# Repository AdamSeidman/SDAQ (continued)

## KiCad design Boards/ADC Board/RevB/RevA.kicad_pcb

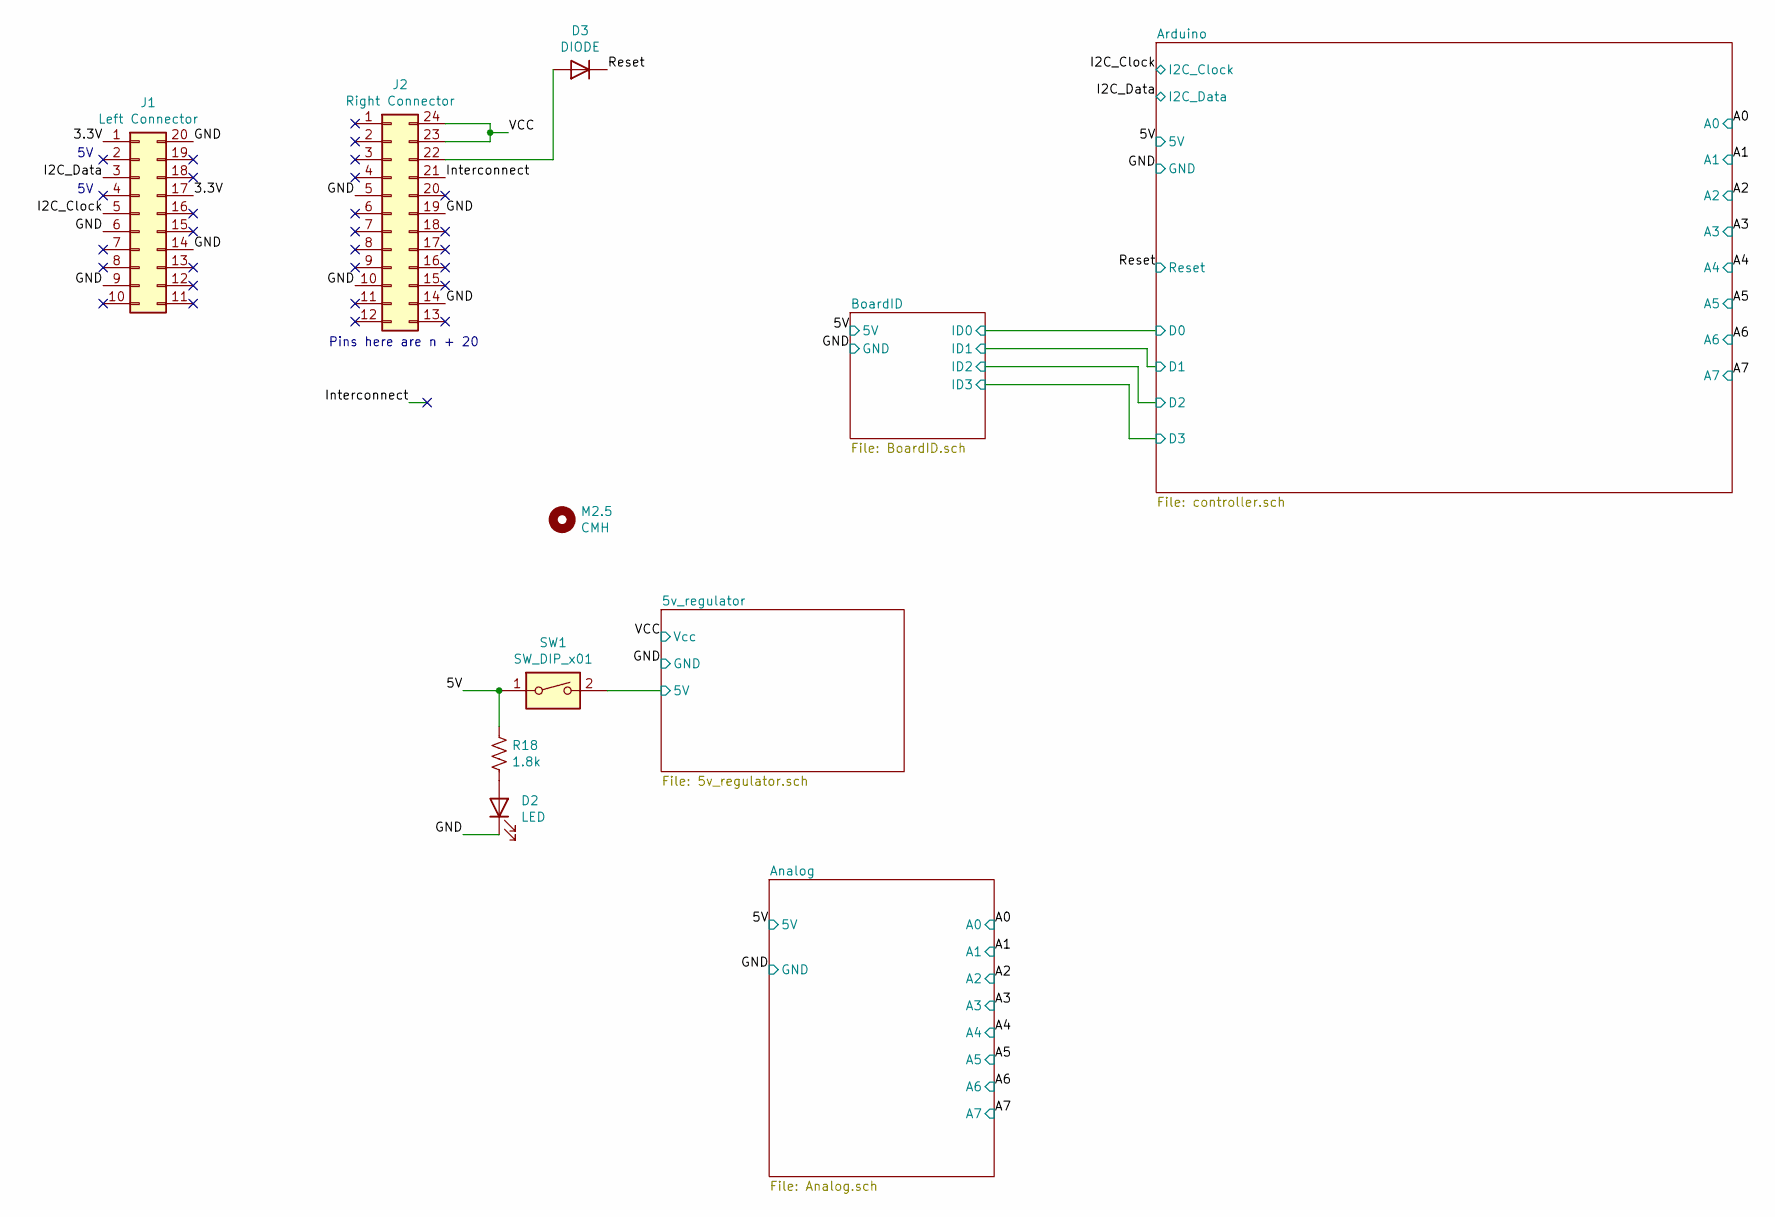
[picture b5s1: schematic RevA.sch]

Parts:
D2: LED; LED_1206_3216Metric
D3: DIODE; D_SMA
J1: Left Connector; PinHeader_2x10_P2.54mm_Vertical
J2: Right Connector; PinHeader_2x12_P2.54mm_Vertical
M2.5: CMH; MountingHole_2.7mm_M2.5
R18: 1.8k; R_0603_1608Metric
SW1: SW_DIP_x01; SW_DIP_SPSTx01_Slide_9.78x4.72mm_W8.61mm_P2.54mm

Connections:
/3.3V: J1.1, J1.17
/5V: R18.1, SW1.1; also elsewhere on the board
/5v_regulator/5V: SW1.2; also elsewhere on the board
/GND: D2.1 (K), J1.6, J1.9, J1.14, J1.20, J2.5, J2.10, J2.14, J2.19; also elsewhere on the board
/I2C_Clock: J1.5; also elsewhere on the board
/I2C_Data: J1.3; also elsewhere on the board
/Interconnect: J2.21
/Reset: D3.2 (K); also elsewhere on the board
/VCC: J2.23, J2.24; also elsewhere on the board
unnamed: D2.2 (A), R18.2
unnamed: D3.1 (A), J2.22

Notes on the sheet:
Pins here are n + 20

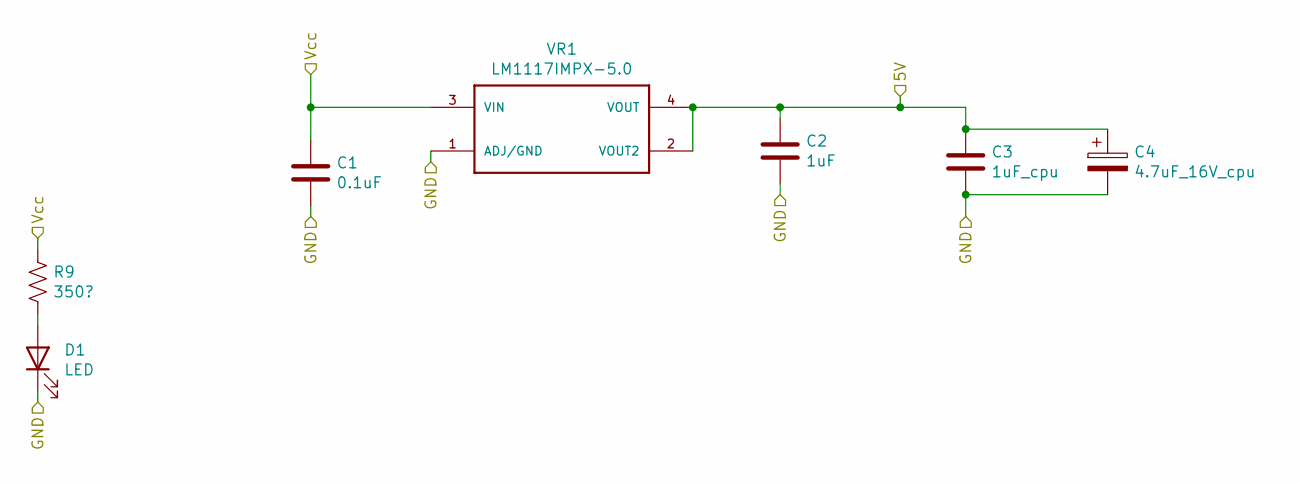
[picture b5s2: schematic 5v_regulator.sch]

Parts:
C1: 0.1uF; C_0603_1608Metric
C2: 1uF; C_0603_1608Metric
C3: 1uF_cpu; C_0603_1608Metric
C4: 4.7uF_16V_cpu; CP_EIA-3216-18_Kemet-A
D1: LED; LED_1206_3216Metric
R9: 350?; R_0603_1608Metric
VR1: LM1117IMPX-5.0; SOT230P700X180-4N

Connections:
/5v_regulator/5V: C2.1, C3.1, C4.1, VR1.2 (VOUT2), VR1.4 (VOUT); also elsewhere on the board
/GND: C1.2, C2.2, C3.2, C4.2, D1.1 (K), VR1.1 (ADJ/GND); also elsewhere on the board
/VCC: C1.1, R9.1, VR1.3 (VIN); also elsewhere on the board
unnamed: D1.2 (A), R9.2

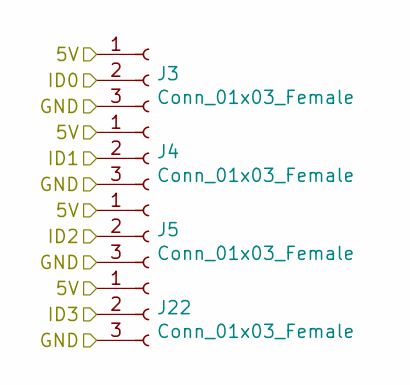
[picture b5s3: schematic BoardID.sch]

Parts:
J3, J4, J5, J22: Conn_01x03_Female; PinHeader_1x03_P1.27mm_Vertical

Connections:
/5V: J3.1, J4.1, J5.1, J22.1; also elsewhere on the board
/Arduino/D0: J3.2; also elsewhere on the board
/Arduino/D1: J4.2; also elsewhere on the board
/Arduino/D2: J5.2; also elsewhere on the board
/Arduino/D3: J22.2; also elsewhere on the board
/GND: J3.3, J4.3, J5.3, J22.3; also elsewhere on the board

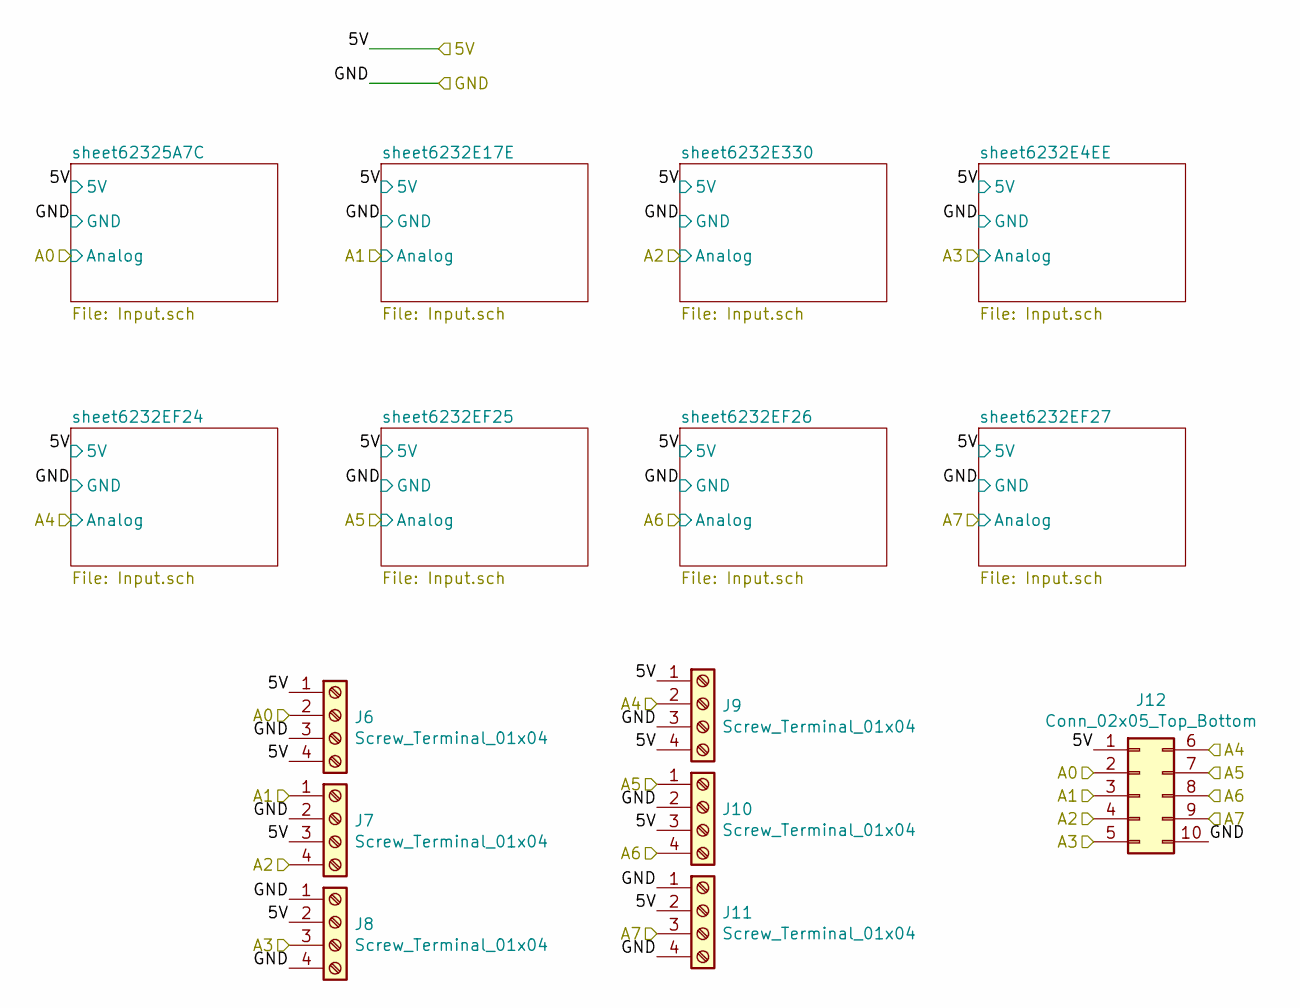
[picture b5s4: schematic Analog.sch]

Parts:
J6, J7, J8, J9, J10, J11: Screw_Terminal_01x04; 1984989
J12: Conn_02x05_Top_Bottom; PinHeader_2x05_P2.54mm_Vertical

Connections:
/5V: J6.1, J6.4, J7.3, J8.2, J9.1, J9.4, J10.3, J11.2, J12.1; also elsewhere on the board
/A0: J6.2, J12.2; also elsewhere on the board
/A1: J7.1, J12.3; also elsewhere on the board
/A2: J7.4, J12.4; also elsewhere on the board
/A3: J8.3, J12.5; also elsewhere on the board
/A4: J9.2, J12.6; also elsewhere on the board
/A5: J10.1, J12.7; also elsewhere on the board
/A6: J10.4, J12.8; also elsewhere on the board
/A7: J11.3, J12.9; also elsewhere on the board
/GND: J6.3, J7.2, J8.1, J8.4, J9.3, J10.2, J11.1, J11.4, J12.10; also elsewhere on the board

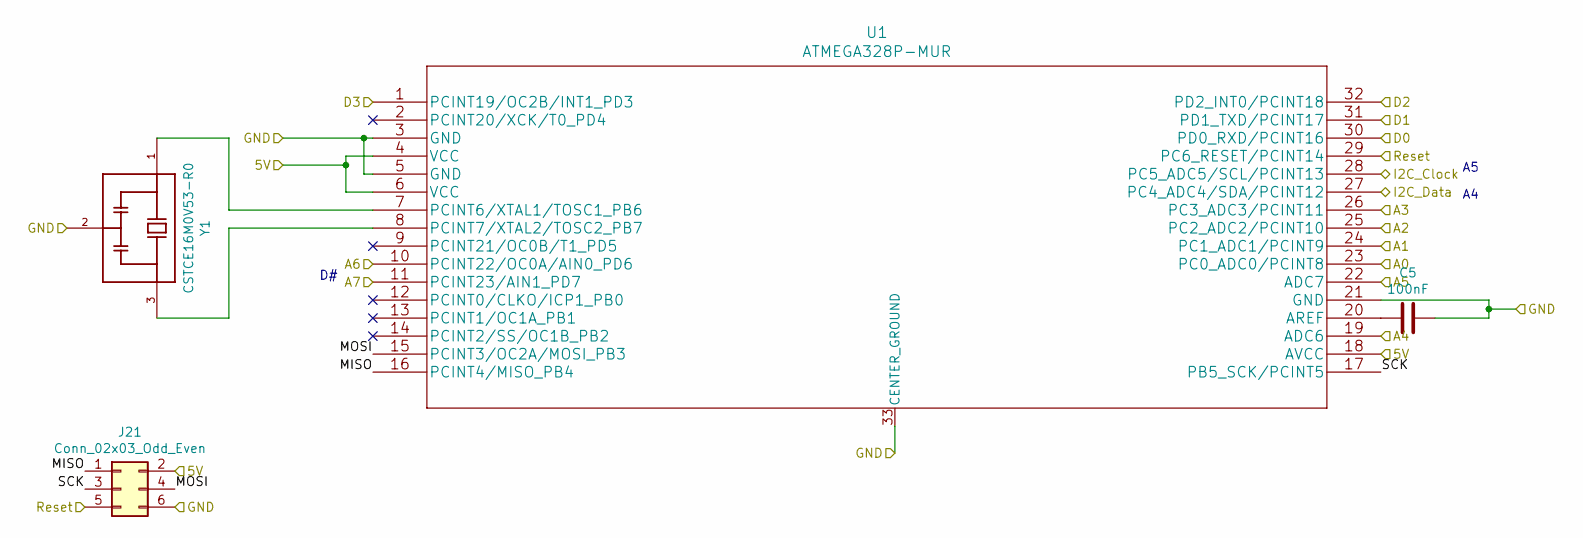
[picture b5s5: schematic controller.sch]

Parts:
C5: 100nF; C_0603_1608Metric
J21: Conn_02x03_Odd_Even; PinHeader_2x03_P2.54mm_Vertical
U1: ATMEGA328P-MUR
Y1: CSTCE16M0V53-R0

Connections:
/5V: J21.2, U1.4 (VCC), U1.6 (VCC), U1.18 (AVCC); also elsewhere on the board
/A0: U1.23 (PC0_ADC0/PCINT8); also elsewhere on the board
/A1: U1.24 (PC1_ADC1/PCINT9); also elsewhere on the board
/A2: U1.25 (PC2_ADC2/PCINT10); also elsewhere on the board
/A3: U1.26 (PC3_ADC3/PCINT11); also elsewhere on the board
/A4: U1.19 (ADC6); also elsewhere on the board
/A5: U1.22 (ADC7); also elsewhere on the board
/A6: U1.10 (PCINT22/OC0A/AIN0_PD6); also elsewhere on the board
/A7: U1.11 (PCINT23/AIN1_PD7); also elsewhere on the board
/Arduino/D0: U1.30 (PD0_RXD/PCINT16); also elsewhere on the board
/Arduino/D1: U1.31 (PD1_TXD/PCINT17); also elsewhere on the board
/Arduino/D2: U1.32 (PD2_INT0/PCINT18); also elsewhere on the board
/Arduino/D3: U1.1 (PCINT19/OC2B/INT1_PD3); also elsewhere on the board
/Arduino/MISO: J21.1, U1.16 (PCINT4/MISO_PB4)
/Arduino/MOSI: J21.4, U1.15 (PCINT3/OC2A/MOSI_PB3)
/Arduino/SCK: J21.3, U1.17 (PB5_SCK/PCINT5)
/GND: C5.1, J21.6, U1.3 (GND), U1.5 (GND), U1.21 (GND), U1.33 (CENTER_GROUND), Y1.2; also elsewhere on the board
/I2C_Clock: U1.28 (PC5_ADC5/SCL/PCINT13); also elsewhere on the board
/I2C_Data: U1.27 (PC4_ADC4/SDA/PCINT12); also elsewhere on the board
/Reset: J21.5, U1.29 (PC6_RESET/PCINT14); also elsewhere on the board
unnamed: C5.2, U1.20 (AREF)
unnamed: U1.7 (PCINT6/XTAL1/TOSC1_PB6), Y1.1
unnamed: U1.8 (PCINT7/XTAL2/TOSC2_PB7), Y1.3

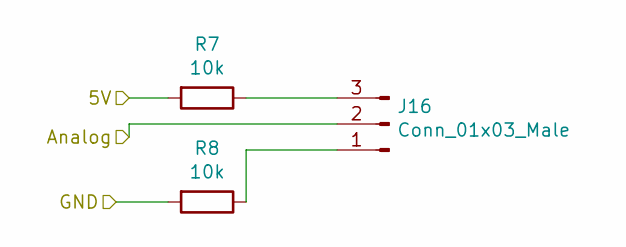
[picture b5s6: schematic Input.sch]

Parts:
J13: Conn_01x03_Male; PinHeader_1x03_P2.54mm_Vertical
R1, R2: 10k; R_0603_1608Metric

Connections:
/5V: R1.2; also elsewhere on the board
/A0: J13.2; also elsewhere on the board
/GND: R2.2; also elsewhere on the board
unnamed: J13.1, R2.1
unnamed: J13.3, R1.1

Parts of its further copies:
J14, J15, J16, J17, J18, J19, J20: Conn_01x03_Male; PinHeader_1x03_P2.54mm_Vertical
R3, R4, R5, R6, R7, R8, R10, R11, R12, R13, R14, R15, R16, R17: 10k; R_0603_1608Metric

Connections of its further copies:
/5V: R3.2, R5.2, R7.2, R10.2, R12.2, R14.2, R16.2; also elsewhere on the board
/A1: J14.2; also elsewhere on the board
/A2: J15.2; also elsewhere on the board
/A3: J16.2; also elsewhere on the board
/A4: J17.2; also elsewhere on the board
/A5: J18.2; also elsewhere on the board
/A6: J19.2; also elsewhere on the board
/A7: J20.2; also elsewhere on the board
/GND: R4.2, R6.2, R8.2, R11.2, R13.2, R15.2, R17.2; also elsewhere on the board
unnamed: J14.1, R4.1
unnamed: J14.3, R3.1
unnamed: J15.1, R6.1
unnamed: J15.3, R5.1
unnamed: J16.1, R8.1
unnamed: J16.3, R7.1
unnamed: J17.1, R11.1
unnamed: J17.3, R10.1
unnamed: J18.1, R13.1
unnamed: J18.3, R12.1
unnamed: J19.1, R15.1
unnamed: J19.3, R14.1
unnamed: J20.1, R17.1
unnamed: J20.3, R16.1

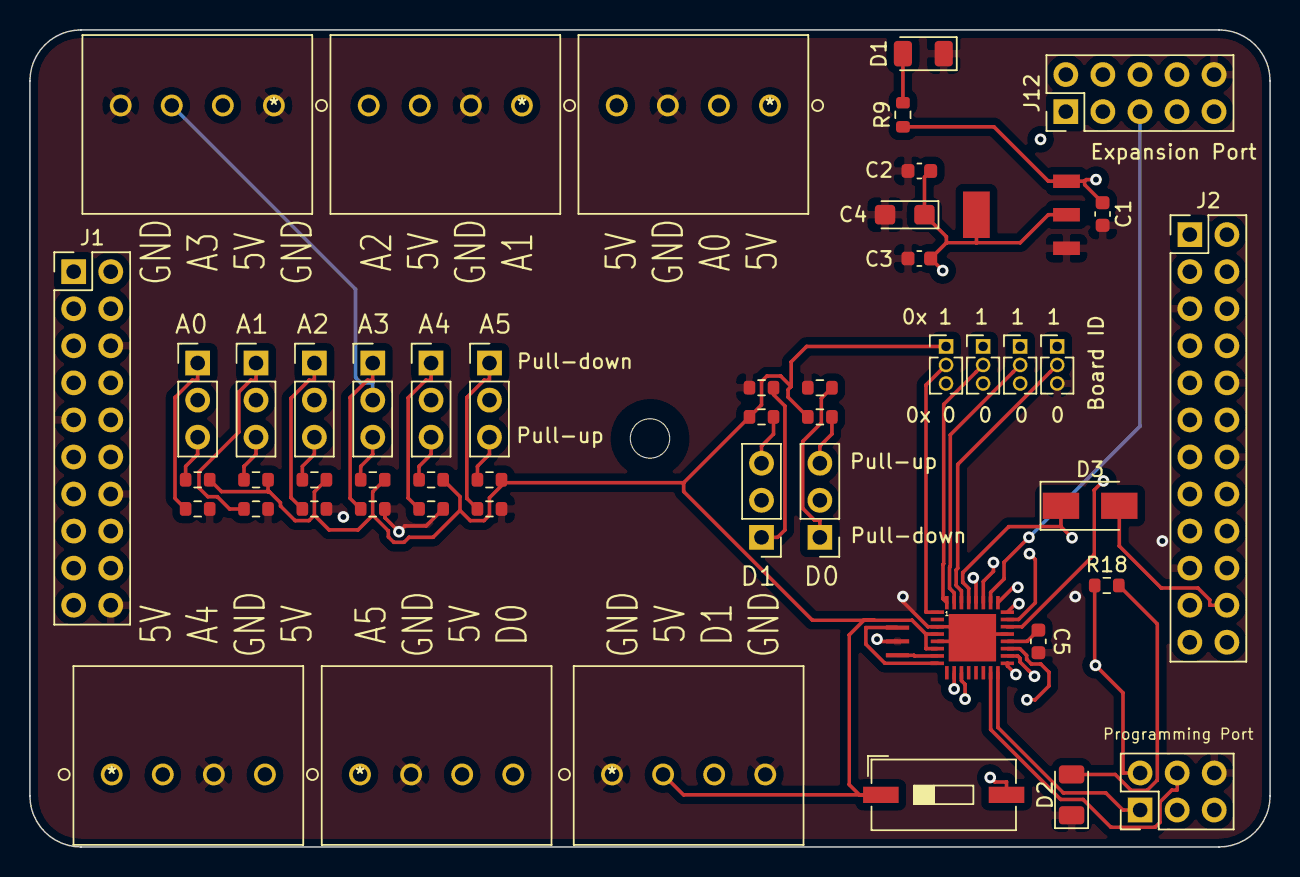
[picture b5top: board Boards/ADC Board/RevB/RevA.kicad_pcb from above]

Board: 4 copper layers, 85.0 x 56.0 mm, 53 parts (0 on the bottom side), 45 nets.

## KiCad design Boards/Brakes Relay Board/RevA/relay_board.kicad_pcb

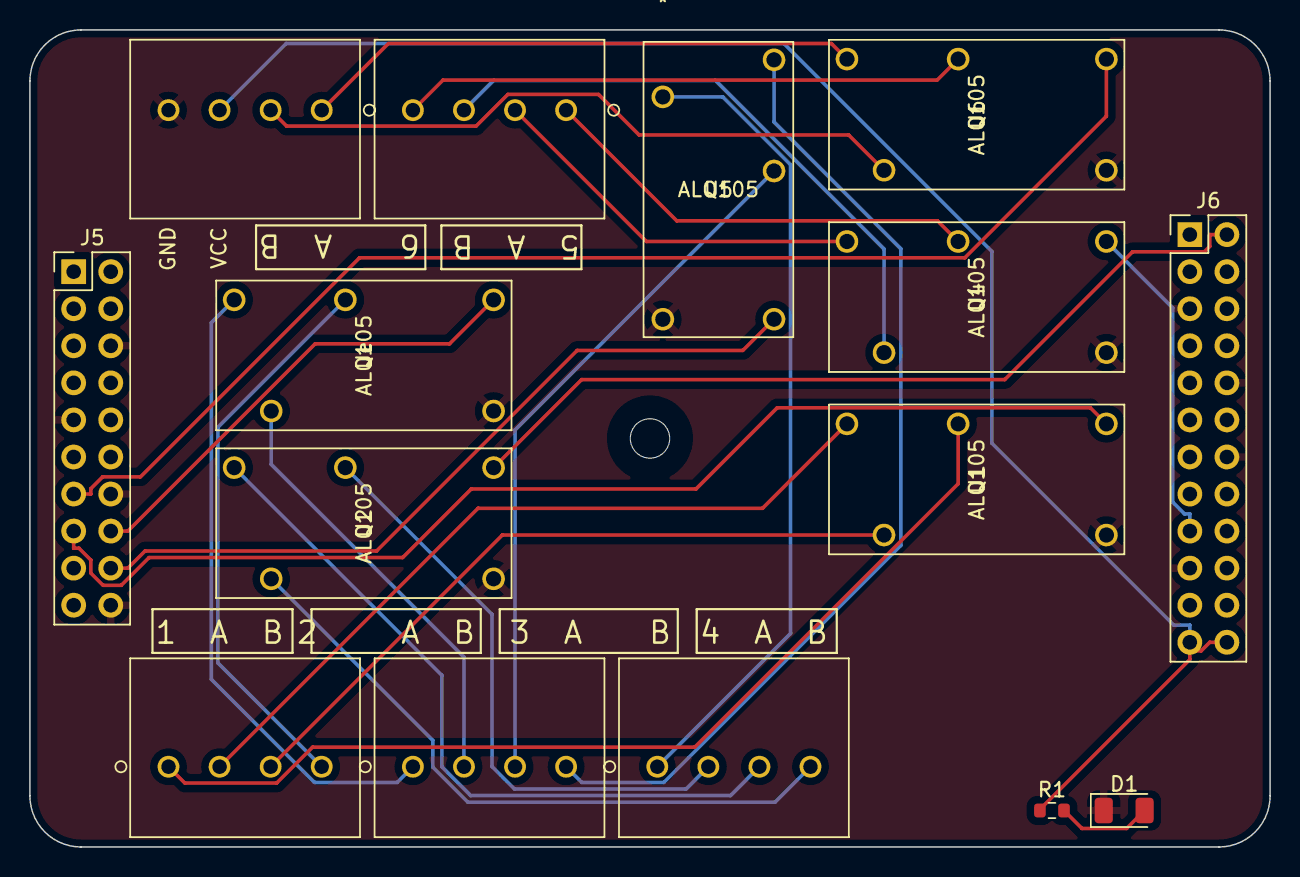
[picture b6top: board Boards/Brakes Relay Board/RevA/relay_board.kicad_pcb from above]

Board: 2 copper layers, 85.0 x 56.0 mm, 15 parts (0 on the bottom side), 27 nets.

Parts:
D1: LED; D_1206_3216Metric
J, J1, J2, J4, J7: Screw_Terminal_01x04; 1984989
J5: Conn_02x10_Counter_Clockwise; PinHeader_2x10_P2.54mm_Vertical
J6: Conn_02x12_Counter_Clockwise; PinHeader_2x12_P2.54mm_Vertical
R1: R; R_0603_1608Metric
U1, U2, U4, U5, U6: ALQ105
Ue: ALQ105

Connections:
/Ch1: J1.1, U1.2
/Ch1A: J1.2, U1.1
/Ch1B: J1.3, U1.5
/Ch2: J1.4, Ue.2
/Ch2A: J2.1, Ue.1
/Ch2B: J2.2, Ue.5
/Ch3: J2.3, U5.2
/Ch3A: J2.4, U5.1
/Ch3B: J.1, U5.5
/Ch4: J.2, U2.2
/Ch4A: J.3, U2.1
/Ch4B: J.4, U2.5
/Ch5: J4.1, U4.2
/Ch5A: J4.2, U4.1
/Ch5B: J4.3, U4.5
/Ch6: J4.4, U6.2
/Ch6A: J7.1, U6.1
/Ch6B: J7.2, U6.5
/GND: D1.1 (K), J5.6, J5.9, J5.14, J5.20, J6.5, J6.10, J6.14, J6.19, J7.4, U1.4, U2.4, U4.4, U5.4, U6.4, Ue.4
/R0: J5.15, U1.3
/R1: J5.16, Ue.3
/R2: J5.18, U5.3
/R3: J6.2, U2.3
/R4: J6.17, U4.3
/R5: J5.13, U6.3
/VCC: J6.23, J6.24, J7.3, R1.1
unnamed: D1.2 (A), R1.2

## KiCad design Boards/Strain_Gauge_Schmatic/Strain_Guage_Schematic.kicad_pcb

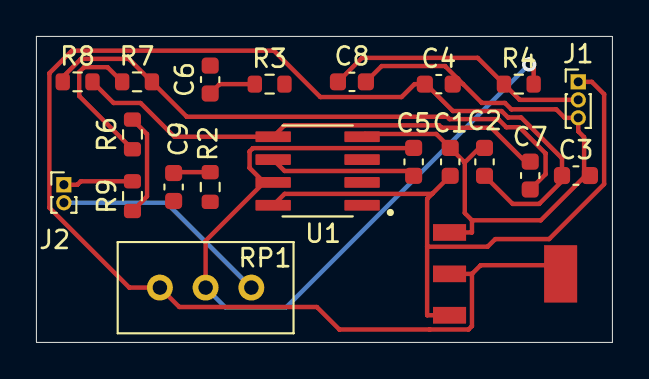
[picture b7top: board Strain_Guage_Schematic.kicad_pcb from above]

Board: 2 copper layers, 32.0 x 17.0 mm, 21 parts (0 on the bottom side), 14 nets.

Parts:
C1: 0.1uF; C_0603_1608Metric
C2: 1uF; C_0603_1608Metric
C3: 1uF_cpu; C_0603_1608Metric
C4: 4.7uF_16V_cpu; C_0603_1608Metric
C5, C6, C7, C8, C9: 100nF; C_0603_1608Metric
J1: Conn_01x03_Male; PinHeader_1x03_P1.00mm_Vertical
J2: Conn_01x02_Male; PinHeader_1x02_P1.00mm_Vertical
R2, R8, R9: 3.6k; R_0603_1608Metric
R3: 10k; R_0603_1608Metric
R4: 47k; R_0603_1608Metric
R6: 22k; R_0603_1608Metric
R7: 470k; R_0603_1608Metric
RP1: R_POT; Potentiometer_Bourns_3296W_Vertical
U1: LM358; SOIC127P599X175-8N
VR1: LM1117IMPX-5.0; SOT230P700X180-4N

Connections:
/Regulator/5V: C2.1, C3.1, C4.1, RP1.3, VR1.2, VR1.4
/Regulator/Vcc: C1.1, J1.1, VR1.3
GND: C1.2, C2.2, C3.2, C4.2, C8.2, J1.3, VR1.1
unnamed: C5.1, U1.6
unnamed: C5.2, R4.2, RP1.2, U1.7
unnamed: C6.1, R3.1
unnamed: C7.1, R7.2, R8.1
unnamed: C7.2, R8.2, U1.5
unnamed: C9.2, R2.1
unnamed: J2.1, R9.2
unnamed: J2.2, RP1.1
unnamed: R6.1, R7.1
unnamed: R6.2, R9.1
Out: C8.1, J1.2, R4.1

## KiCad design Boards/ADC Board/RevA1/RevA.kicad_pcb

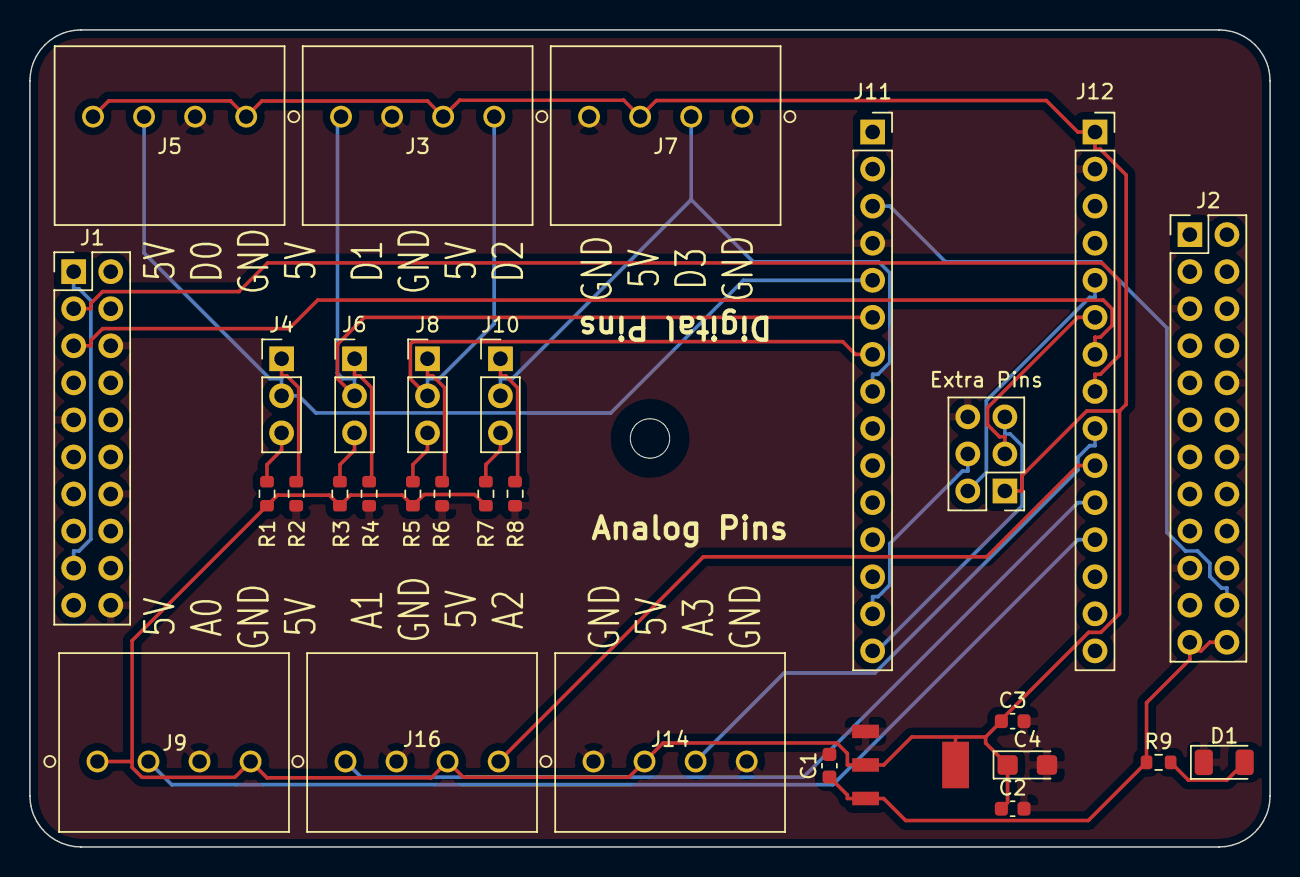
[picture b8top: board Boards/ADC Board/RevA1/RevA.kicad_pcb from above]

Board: 2 copper layers, 85.0 x 56.0 mm, 31 parts (0 on the bottom side), 28 nets.

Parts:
C1: 0.1uF; C_0603_1608Metric
C2: 1uF; C_0603_1608Metric
C3: 1uF_cpu; C_0603_1608Metric
C4: 4.7uF_16V_cpu; CP_EIA-3216-18_Kemet-A
D1: LED; LED_1206_3216Metric
J1: Left Connector; PinHeader_2x10_P2.54mm_Vertical
J2: Right Connector; PinHeader_2x12_P2.54mm_Vertical
J3, J5, J7, J9, J14, J16: Screw Terminals; 1984989
J4, J6, J8, J10: Jumper Terminals; PinHeader_1x03_P2.54mm_Vertical
J11: Arduino Nano L; PinSocket_1x15_P2.54mm_Vertical
J12: Arduino Nano R; PinSocket_1x15_P2.54mm_Vertical
J13: Extra Pins; PinHeader_2x03_P2.54mm_Vertical
M2.5: CMH; MountingHole_2.7mm_M2.5
R1, R2, R3, R4, R5, R6, R7, R8: 10k; R_0603_1608Metric
R9: 350?; R_0603_1608Metric
VR1: LM1117IMPX-5.0; SOT230P700X180-4N

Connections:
/3.3V: J1.1, J1.17
/5V: C2.1, C3.1, C4.1, J3.2, J5.1, J5.4, J7.3, J9.1, J9.4, J12.1, J13.1, J14.2, J16.3, R1.2, R3.2, R5.2, R7.2, VR1.2, VR1.4
/Analog_0: J9.2, J12.12
/Analog_1: J12.11, J16.1
/Analog_2: J12.10, J16.4
/Analog_3: J12.9, J14.3
/Controller/A6: J12.6, J13.3
/Controller/A7: J12.5, J13.2
/Controller/D11: J11.14, J13.4
/Controller/D12: J11.15, J13.5
/Digital_0: J4.2, J5.3, J11.5
/Digital_1: J3.4, J6.2, J11.6
/Digital_2: J3.1, J8.2, J11.7
/Digital_3: J7.2, J10.2, J11.8
/GND: C1.2, C2.2, C3.2, C4.2, D1.1, J1.6, J1.9, J1.14, J1.20, J2.5, J2.10, J2.14, J2.19, J3.3, J5.2, J7.1, J7.4, J9.3, J11.4, J12.2, J13.6, J14.1, J14.4, J16.2, R2.2, R4.2, R6.2, R8.2, VR1.1
/I2C_Clock: J1.5, J12.7
/I2C_Data: J1.3, J12.8
/Reset: J2.22, J11.3
/VCC: C1.1, J2.23, J2.24, R9.1, VR1.3
unnamed: D1.2, R9.2
unnamed: J4.1, R2.1
unnamed: J4.3, R1.1
unnamed: J6.1, R4.1
unnamed: J6.3, R3.1
unnamed: J8.1, R6.1
unnamed: J8.3, R5.1
unnamed: J10.1, R8.1
unnamed: J10.3, R7.1

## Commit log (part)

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2021-09-23 Added Rough Layout
2021-09-24 Start of PI and μV board schematics
2021-09-24 Added thermocouple sheet
    Also moved around some stuff for clarity, and added some text.
2021-10-02 Created Rev_B of the MicroVolt Board. Edited RevA of ADC Board.
    Deleted CAN infrastructure in Rev_B, and added I2C "infrastructure." Better labeled arduino nano pins within controller sheet. Imported pins from controller sheet out to board. Added controller, pull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
2021-10-08 Copied controller board from micro board to ADC board. Created pull up/down sheets and populated them.
    Also copied over main set of header pins into ADC sheet.
2021-10-08 Initial Main Board Upload
2021-10-08 Added 5V Regulator Schematic
2021-10-08 Added Mounting Holes to Main Board
2021-10-08 Added a Majority of Main Board Footprints
2021-10-08 Added regulator to ADC and micro boards. Added actual connectors for the strain gauge modules.
2021-10-08 Added \#Parts
    (For 5V Regulator)
2021-10-08 Fixed LM1117 Symbol
2021-10-08 Update LM1117IMPX-5.0.lib
    Pin Naming Change
2021-10-08 Created Main Board PCB Template
2021-10-08 Fixed regulator nonsense on ADC board. Rules checked both ADC and micro boards. Fixed interconnect on ADC board.
2021-10-08 Roughed out Main Board PCB
2021-10-08 Updated .dsn Files and Power Planes/Keepouts for Main Board
2021-10-08 Finished Main Board Routing
    Made 4 Layers
2021-10-10 Began PCB layout for ADC board. Fixed annotations for ADC and micro boards.
2021-10-10 Copied RevA Board to \RevA1
2021-10-10 Removed Main Board Gerber.zip
2021-10-11 Completed footprint associations for ADC board. Generated netlist for ADC board. Started PCB design for ADC board.
2021-10-12 Create placeholder
2021-10-12 /RevA1 Board Set up For Auto-Routing
2021-10-12 Added Gerber Files and Main_Board.xlsx
2021-10-13 Move Baja_Pi_Expansion-RevA.zip
2021-10-15 Created order excel form.
2021-10-15 Finished order sheet.
2021-10-17 Completed Main Board Routing with 3.5 mm Connectors
2021-10-17 Completed Main Board Revision A
2021-10-22 Determined correct spacing for Arduino nano pins. Placed down voltage regulator and associated components.
2021-11-23 Imported 4 pin spring terminals. Replaced 12 pin terminals with 4 pin terminals on ADC board. Placed 4 pin terminals on PCB.
2022-01-22 Moved around components on the ADC board PCB. Assigned footprints to microVolt board components.
    Tried to add 6-pin spring connector to custom schematics list.
2022-02-03 Prototype reversed enginnered schmatic of the strain gauge + IMU board
2022-02-03 Finished placing and organizing PCB components for the ADC board, and prepped board for auto-routing.
2022-02-03 Exported ADC to spectra design file, beginning first autorouting.
2022-02-03 Added Gerber Files for ADC revA
2022-02-03 Main Board: Copied RevA1 into RevB
2022-02-03 Updated Main-RevB annotations and added placeholder for Breadboard_Testbed
2022-02-03 Removed footprints from PCB on Main-RevB
2022-02-03 Turned Main-RevB from 4 layers into 2
2022-02-03 Begin to put components in place on Main-RevB
2022-02-03 Finished placing most components: Main-RevB
2022-02-03 Begin Breadboard-Testbed RevA
2022-02-03 Finished Breadboard-Testbed RevA Schematic
2022-02-03 Generated Netlist for Breadboard-Testbed
2022-02-04 Finished Test-RevA layout Pre-route
2022-02-04 Routing Complete Test-RevA board
2022-02-04 Added gerber files for Breadboard_Testbed-RevA
2022-02-04 Breadboard-test save files
2022-02-04 Finalized Main-RevB board
2022-02-04 [ImgBot] Optimize images
    *Total -- 1,016.30kb -> 924.98kb (8.99%)
    /Boards/Breadboard_Testbed/RevA/Gerber/Breadboard_Testbed-RevA.png -- 236.40kb -> 212.63kb (10.06%)
    /Boards/Main Board/#Gerber/pcb_options.png -- 139.95kb -> 126.25kb (9.79%)
    /Boards/ADC Board/RevA1/Gerber/SDAQ_ADC_Board_RevA.png -- 476.82kb -> 434.37kb (8.9%)
    /Boards/Main Board/#Gerber/#Zips/Main_Board-RevB.png -- 163.13kb -> 151.74kb (6.98%)
2022-02-05 In process of updating ADC board to remove 5V connection from PI. Also commiting small changes to uV board.
2022-02-05 Finished the reassociation of the PI pins, created the .dril and Gerber files and zipped them up.
2022-02-05 Fixed Main-RevB autorouting
2022-02-05 Updated Main-RevB Gerbers
2022-02-05 [ImgBot] Optimize images
    /Boards/Main Board/#Gerber/#Zips/Main_Board-RevB.png -- 496.19kb -> 379.79kb (23.46%)
2022-02-05 New strain gauge schematic + pcb
2022-02-07 Initial commit for GUI and its layout
2022-02-11 Added capacitor resistances
2022-02-12 Began the schmatic of the Xsense implemented with a arduino nano, added LED's to indcate board is powered
2022-02-19 Designed and implemented first version of SDAQ GUI
    No functionalities yet
    Added GPIO Pins into Resources
2022-02-25 Added template for arduino code
2022-02-26 Split i2c-test into i2c-read and i2c-scan
    i2c-read and i2c-scan will be used with scheduler in gui.py
    Changed config.ini to be split by commas for board name and ID (used for comparison and i2c; e.g. which board is connected and display it dropdown menu).
2022-02-28 Updated Titles for Plots
2022-02-28 Finished Analog test interface for I2C (and ADC board)
2022-03-04 Played with Data Rates and Refactored
2022-03-11 Updated ino and Added python tools from RTS convert
2022-03-12 Updated lib tools to be Logical
2022-03-16 Created ADC board RevB
2022-03-16 Cleanup before pcb
2022-03-18 Created PCB for Rev B
2022-03-18 Continued making RevB PCB
2022-03-21 Completed RevB autorouting
2022-03-22 Finished rev B routing and screenshots
2022-03-25 Created Relay Board RevA
2022-03-25 Relay Board RevA Rough PCB
2022-03-25 Created Design File for Relay Board Rev A
2022-03-25 Added Screw Terminal Labels for Relay Board Rev a
2022-03-25 Relay Board Rev A Complete
2022-03-25 Created Gerber Zip for Relay Board Rev A
2022-03-25 Added Main-RevC Zip
2022-03-25 Placeholder for Strain Passthrough (RevA)
2022-03-26 Added Strain Gauge Schematic
    Added Strain Gauge Schematic with notes. Determined only thing needed to change was +5V regulator.
2022-03-26 Strain Gauge Schematic
    Initial creation of strain gauge schematic. Has some parts missing relating to sensor and outputs.
2022-03-26 Added everything from SDAQ
    Worked on GUI for RPM Data Collector
    Worked on generic GUI for all boards
    Implemented valueFrame for putting options for RPM's GUI
    Fixed issues in shift_around_val and added combine_data (for avg) in tools.py
    Added cat jam
2022-03-30 Pull from SDAQ with recent changes. Made order for SDAQ and Brakes PCBs.
2022-03-30 Added ctWriter, and fixed other issues with UI
2022-03-30 Add a (very unfinished) viewer for CT files
2022-03-31 Add a lot more functionality, but no GUI stuffs
2022-03-31 Add notes info
2022-03-31 Actually moved the csv into the Orders sheet
2022-03-31 Updated order sheet name
2022-03-31 Add signficiant improvements
2022-03-31 Working?
2022-03-31 Everything works!
2022-04-01 Add a helper library
2022-04-01 Added Main_RevD with New Board
2022-04-03 Fix plot system to be scrollable, remove extraneous files
2022-04-04 Fix issues related to objects being incorrect
    There are also sorting fixes to ensure that sorting is 100% correct and
    good, with two options to sort
2022-04-18 Attempted to fix strain guage algorithm
2022-04-19 Added missing Brakes-Parse code
2022-04-21 Updated tools.py
    Added test algorithms. Comments that say "this works" are algorithms with most progress.
2022-04-21 Updated file.py to StrainGauge.py
    Renamed file.py to StrainGauage.py. Also updated to work with newest algorithms.
2022-04-21 Added strain_parse_testing.py
    Also created a new parse folder and moved parsing files in there.
2022-04-21 Created centralized folder for SDAQ data, and populated it with 4/20 data.
2022-04-21 Neither of these work
2022-04-21 Complete Refactor Overhaul
2022-04-21 Updated logic and refactored rollover functions for strain
2022-04-21 Rename the example folder to betteer reflect purpose
2022-04-22 Adding constants for rollover fixing (live)
    (Adam)
2022-04-22 Attempting to give a better overview
2022-04-22 Uploaded low end calibration data
2022-04-22 Made small algorithm changes
2022-04-22 Made strain_part_testing Generic
2022-04-22 Added comment for override paths
2022-04-23 Minor Readability Changes to Pressure.py
2022-04-23 Uploaded data for 4/22 calibration
2022-04-24 Adding Raw Data from 4/22
2022-04-24 Added annotations for graphing.Plot
2022-04-24 Updated tools.apply_strain_calibrations for intercept
2022-04-25 Move Shock/Link 5 Mock Scripts to /Parse/Final
2022-04-25 Added garbage tie rod data
2022-05-28 Added mosfet to relay and 5V regulator to schematic
2022-05-28 Added new components to PCB
2022-05-28 Routed relay board rev b
2022-07-12 Not sure what this is, but you guys might want it
2022-07-12 Don't know what this stuff is either, merge it if you want
2022-11-05 Add in new data tracking files for collecting thermistor data
2022-11-05 Add in work on new-type strain gauge with differential ADC
2022-11-05 Get files off my laptop and into the world
2022-11-19 Add the newest work for the strain gauge module
    Work will continue for this soon for getting maximal value out of the
    system.
2022-11-19 Slightly update the schematic
2022-11-23 Fix clutch tune viewer for valid consumption
2022-12-14 Added schematic changes to pull in the mainboard
2022-12-14 0603 more things
2023-01-03 PCB Design process should be beginning soon
2023-01-05 Hopefully a good layout for the board
2023-01-05 More strain gauge work to get in-stock parts
2023-01-05 Make the USB differential pairing better
2023-01-05 Improve differential pairing.
2023-01-06 It's apparently possible to communicate over SPI to the ADC
2023-01-06 More micro-adjustments and add the I2C lines
2023-01-07 Remove a LOT of signal noise on the oscillator
2023-01-07 Anti-emi Aktion
2023-01-07 Micro-optimized it all.
2023-01-08 Begin working on the pico driver
2023-01-08 More pico development, hopefully correct board info
2023-01-09 A lot more code such that the software might work on first arrival
2023-01-09 Filter the voltage input to the system
2023-01-10 Might actually have finished the code for the board
2023-01-10 Hopefully final revision
2023-01-10 More micro-changes without finishing the BOM
2023-01-10 Near finished with BOM selection
2023-01-10 Finish basic BOM and update desc. in pcb
2023-01-11 Fix the pico driver to decode packets correctly
2023-01-15 Better BOM and more accurate to final design schematic, little will change from this.
2023-01-18 Switch to standard pin header widths.
2023-01-21 Make obvious what item is what in the SDAQ
    Also add in my old headless DAQ code that is useful for non-attena constrained environments
2023-01-22 Fix PWR SNS GND labels so that they are more accurate to the new design.
2023-01-24 Add RIT Baja SAE offical logo to the Stain Gauge board
2023-03-29 Update to allow for a primary RPM sensor to be used when we want to select it
2023-04-08 Fix pretty much everything known
2023-04-08 Working mutli-item RPM data
2023-06-30 Ensure strain gauge board uses cheaper components
2023-06-30 More interesting changes
2023-08-21 Update to latest code and board design. Include things like a purchase link for the DIP switch and closer to functional I2C.
2023-08-31 Updated strain gauge V2 to have a button
    I need to update the button to be closer to ones we already have however.
2023-09-16 Update board to use two voltage references
    This will be a "demo" for a two-reference board, next I will most likely
    design one with a differential instrumentation amplifier before
    having a new board with 4 instrumentation amplifiers and a single-ended
    ADC involved.
